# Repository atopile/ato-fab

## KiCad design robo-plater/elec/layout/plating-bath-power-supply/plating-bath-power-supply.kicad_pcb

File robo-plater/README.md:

# robo-plater

A robot to manage plating PCBs

# Circuit Design

## Motor Driver

The feedback for the motor driver is fun. We use the fact that DC brushed motors means there's a convenient current ripple from the mechanical commutation. If we count the pulses in the current ripple, we can determine the position of the motor.

You can make a very simple circuit to do this using a single op-amp, and some discretes, but I've used a second op-amp here because even the cheapest packages seem to come with at least two op-amps.

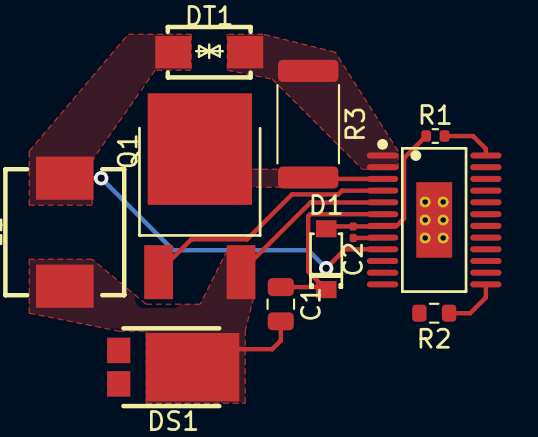
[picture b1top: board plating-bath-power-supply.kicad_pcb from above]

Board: 2 copper layers, 11 parts (0 on the bottom side), 10 nets.

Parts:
C1: 50V 150nF X7R ±10% 0805 Multilayer Ceramic Capaci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; C0805
C2: 6.3V 3uF X5R ±20% 0201 Multilayer Ceramic Capacit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; C0201
D1: ?; SOD-123_L2.8-W1.8-LS3.7-RD
DS1: ?; TO-277B-3_L5.4-W4.1-P1.85-LS6.5-TR
DT1: ?; SMA_L4.4-W2.6-LS5.0-BI
L1: ?; IND-SMD_L7.0-W6.6
Q1: ?; TO-252-2_L6.6-W6.1-P4.57-LS9.9-BR-CW
R1: 62.5mW Thick Film Resistors 50V ±800ppm/℃ ±1% 0Ω 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; R0402
R2: 100mW Thick Film Resistors 75V ±100ppm/℃ ±1% 10kΩ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; R0603
R3: ?; R2512
U1: ?; HTSSOP-24_L7.8-W4.4-P0.65-BL-EP

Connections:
boot1: C1.1, D1.1, U1.6
csn1: Q1.2, R3.2, U1.3
en_uv: R1.1, U1.24
gate1: Q1.1, U1.4
gnd: C2.2, DS1.1, DS1.3, U1.8, U1.17
miso: R2.1, U1.13
sw1: C1.2, DS1.2, L1.1, Q1.3, U1.5
vcc1: C2.1, D1.2, R1.2, U1.7
vcc-1: DT1.1, R3.1, U1.1, U1.2
vcc-2: DT1.2, L1.2, U1.9

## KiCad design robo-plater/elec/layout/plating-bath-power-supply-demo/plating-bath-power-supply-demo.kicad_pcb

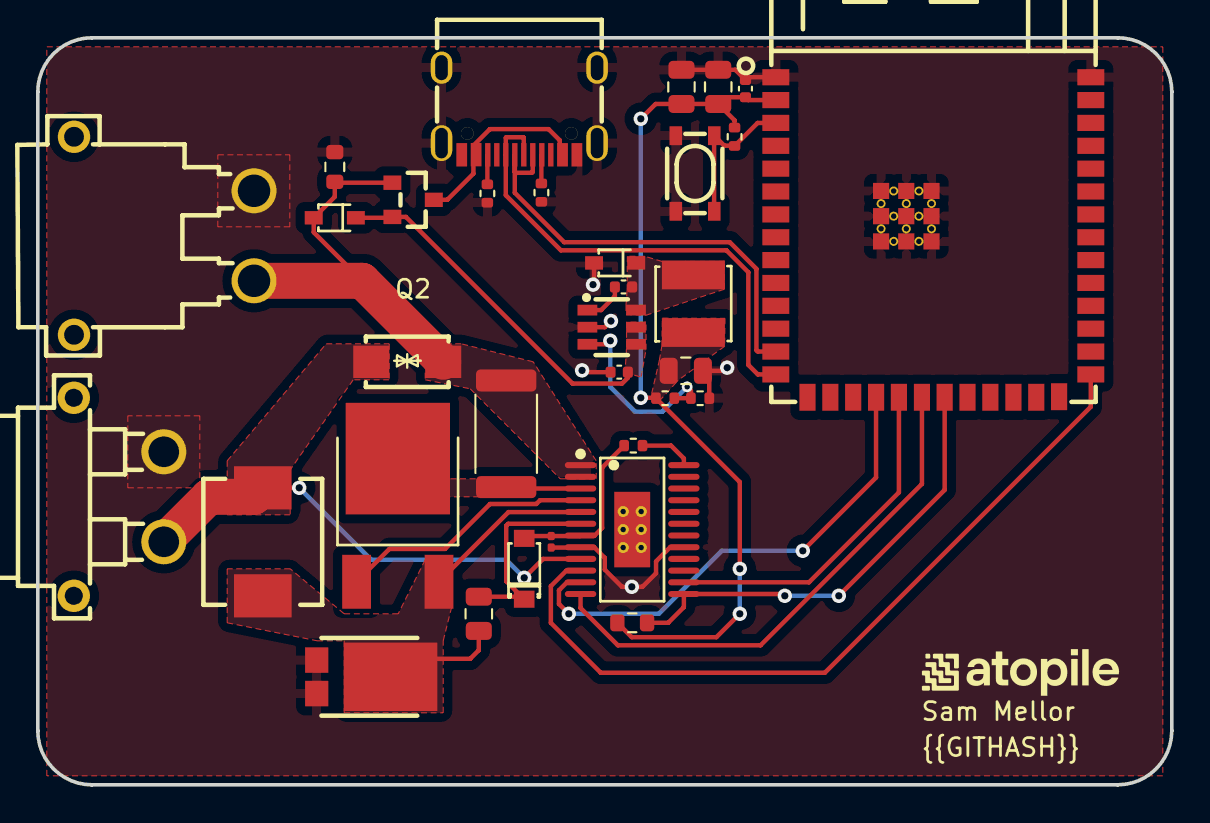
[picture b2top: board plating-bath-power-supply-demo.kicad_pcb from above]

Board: 2 copper layers, 63.0 x 41.5 mm, 33 parts (0 on the bottom side), 25 nets.

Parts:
C1: 6.3V 10uF X5R ±20% 0402 Multilayer Ceramic Capaci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; C0402
C2, C5, C6: 25V 10uF X5R ±10% 0805 Multilayer Ceramic Capacit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; C0805
C3, C4: 16V 100nF X7R ±10% 0402 Multilayer Ceramic Capaci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; C0402
C7: 50V 150nF X7R ±10% 0805 Multilayer Ceramic Capaci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; C0805
C8: 6.3V 3uF X5R ±20% 0201 Multilayer Ceramic Capacit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; C0201
D1: ?; SOD-123_L2.8-W1.8-LS3.7-RD
DS1, DS3: ?; SOD-323_L1.8-W1.3-LS2.5-RD
DS2: ?; TO-277B-3_L5.4-W4.1-P1.85-LS6.5-TR
DT1: ?; SMA_L4.4-W2.6-LS5.0-BI
J1: ?; CONN-TH_XT30PW-M
L1: ?; IND-SMD_L4.0-W4.0
L2: ?; IND-SMD_L7.0-W6.6
Q1: ?; TO-252-2_L6.6-W6.1-P4.57-LS9.9-BR-CW
Q2: ?; SOT-23_L2.9-W1.3-P1.90-LS2.4-BR
R1, R2: 62.5mW Thick Film Resistors 50V ±100ppm/℃ ±1% 4.7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; R0402
R3: 62.5mW Thick Film Resistors 50V ±100ppm/℃ ±1% 14.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; R0402
R4: 62.5mW Thick Film Resistors 50V ±100ppm/℃ ±1% 4.3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; R0402
R5: 62.5mW Thick Film Resistors 50V ±100ppm/℃ ±1% 10k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; R0402
R6: 62.5mW Thick Film Resistors 50V ±800ppm/℃ ±1% 0Ω 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; R0402
R7, R9: 100mW Thick Film Resistors 75V ±100ppm/℃ ±1% 10kΩ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; R0603
R8: ?; R2512
U1: ?; USB-C-SMD_KH-TYPE-C-16P
U2: 0.6A, 42V, 1.1MHz Buck Regulator; SOT-23-6_L2.9-W1.6-P0.95-LS2.8-BR
U3: ?; WIRELM-SMD_ESP32-S3-WROOM-1
U4: ?; KEY-SMD_4P-L4.2-W3.2-P2.20-LS4.6
U5: ?; HTSSOP-24_L7.8-W4.4-P0.65-BL-EP
U6: ?; CONN-TH_XT30PW-F-1

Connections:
boot1: C7.1, D1.1, U5.6
cb: C3.1, U2.1
cc1: R1.1, U1.A5
cc2: R2.1, U1.B5
cs: U3.18, U5.11
csn1: Q1.2, R8.2, U5.3
dm: U1.A7, U1.B7, U3.13
dp: U1.A6, U1.B6, U3.14
en: R5.2, U3.3, U4.1, U4.2
en_uv: R6.1, U5.24
gate1: Q1.1, U5.4
io0: U3.27, U5.10
miso: R7.1, U3.21, U5.13
mosi: U3.19, U5.14
out: R3.2, R4.1, U2.3
plating_supply-vcc: DT1.2, L2.2, U5.9, U6.2
regulator-vcc: C1.1, DS3.1, Q2.2, U2.4, U2.5
regulator-vcc-1: C2.1, C4.1, C5.1, C6.1, L1.2, R3.1, R5.1, R7.2, U3.2
sck: U3.20, U5.12
sw: C3.2, DS1.1, L1.1, U2.6
sw1: C7.2, DS2.2, L2.1, Q1.3, U5.5
usb_conn-vcc: Q2.3, U1.A4, U1.A9, U1.B4, U1.B9
vcc1: C8.1, D1.2, R6.2, U5.7
xt30_input-gnd: C1.2, C2.2, C4.2, C5.2, C6.2, C8.2, DS1.2, DS2.1, DS2.3, J1.1, R1.2, R2.2, R4.2, R9.2, U1.1, U1.2, U1.3, U1.4, U1.A1, U1.A12, U1.B1, U1.B12, U2.2, U3.1, U3.40, U3.41, U4.3, U4.4, U5.8, U5.17, U6.1
xt30_input-vcc: DS3.2, DT1.1, J1.2, Q2.1, R8.1, R9.1, U5.1, U5.2

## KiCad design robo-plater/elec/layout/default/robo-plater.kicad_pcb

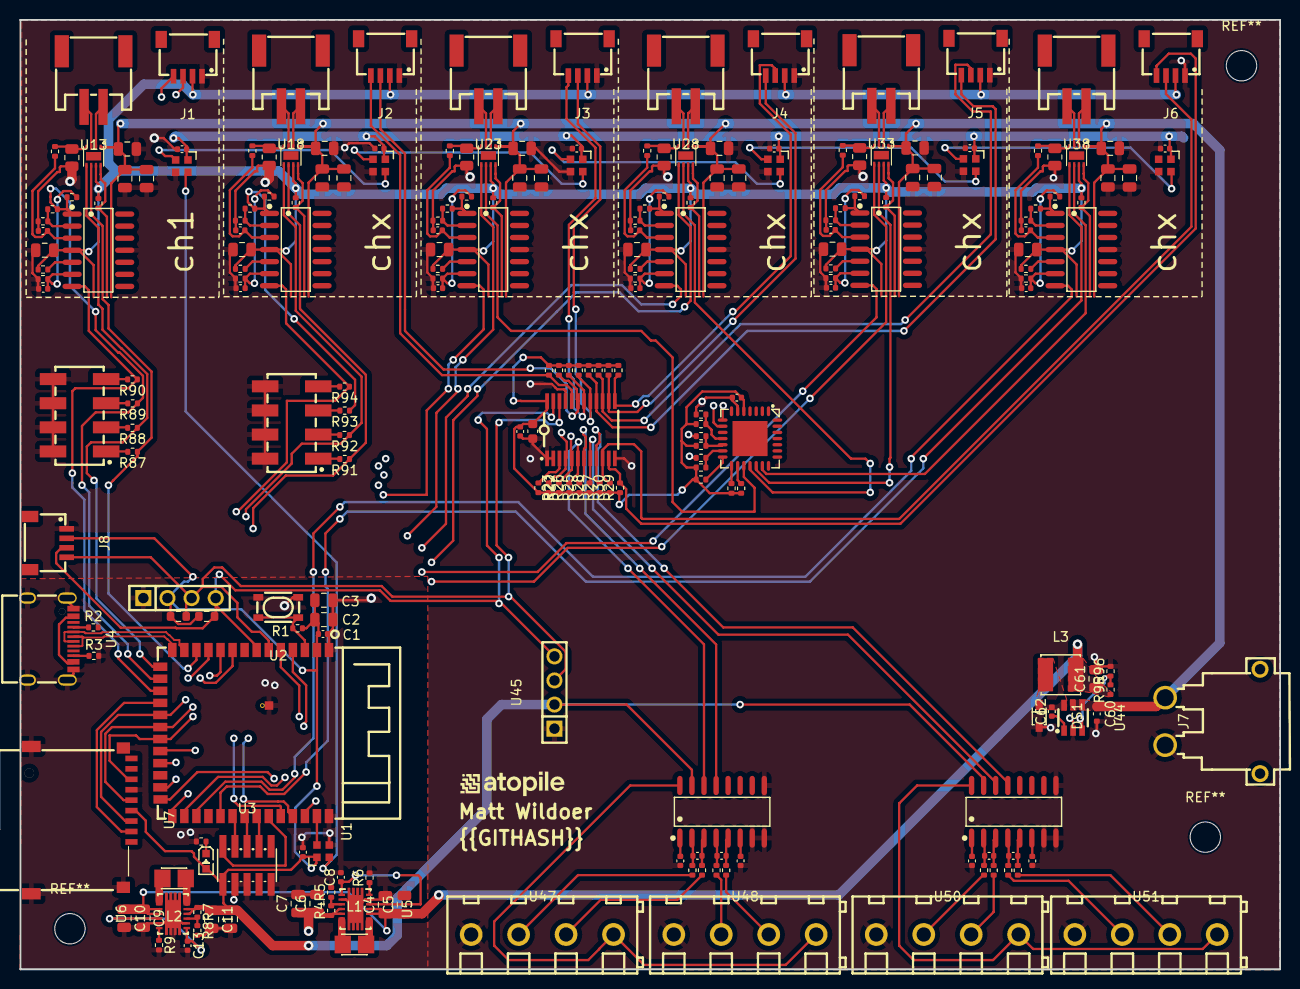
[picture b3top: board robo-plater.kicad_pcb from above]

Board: 4 copper layers, 132.7 x 100.0 mm, 238 parts (0 on the bottom side), 174 nets.

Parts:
C1, C8, C13, C14, C15, C16, C22, C24, C29, C31, C36, C38, C43, C45, C50, C52, C57, C59, C62, C63, C64, C65, C66, C67, C68, C69, C70: 16V 100nF X7R ±10% 0402 Multilayer Ceramic Capaci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; C0402
C2, C3, C4, C5, C6, C7, C9, C10, C11, C12, C18, C19, C20, C21, C25, C26, C27, C28, C32, C33, C34, C35, C39, C40, C41, C42, C46, C47, C48, C49, C53, C54, C55, C56, C61: 25V 10uF X5R ±10% 0805 Multilayer Ceramic Capacit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; C0805
C17: 16V 2.2uF X5R ±10% 0603 Multilayer Ceramic Capaci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; C0603
C23, C30, C37, C44, C51, C58: 25V 1uF X5R ±10% 0402 Multilayer Ceramic Capacito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; C0402
C60: 6.3V 10uF X5R ±20% 0402 Multilayer Ceramic Capaci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; C0402
DS1: ?; SOD-323_L1.8-W1.3-LS2.5-RD
J1, J2, J3, J4, J5, J6, J8: ?; CONN-SMD_4P-P1.00_SM04B-SRSS-TB-LF-SN
J7: ?; CONN-TH_XT30PW-M
L1, L2: ?; IND-SMD_L2.5-W2.0_WPN252012H
L3: ?; IND-SMD_L4.0-W4.0
LED1: ?; LED0603-RD
R1, R13, R14, R15, R16, R17, R18, R19, R20, R21, R22, R23, R24, R25, R26, R27, R28, R29, R30, R31, R32, R33, R34, R35, R36, R37, R38, R39, R47, R55, R63, R71, R79: 62.5mW Thick Film Resistors 50V ±100ppm/℃ ±1% 10k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; R0402
R2, R3: 62.5mW Thick Film Resistors 50V ±100ppm/℃ ±1% 4.7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; R0402
R4: 62.5mW 50V ±100ppm/℃ ±1% 25.5kΩ 0402 Chip Resisto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; R0402
R5: 62.5mW Thick Film Resistors 50V ±100ppm/℃ ±1% 2.8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; R0402
R6, R9, R45, R46, R53, R54, R61, R62, R69, R70, R77, R78, R85, R86: 62.5mW Thick Film Resistors 50V ±100ppm/℃ ±1% 1MΩ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; R0402
R7, R95: 62.5mW Thick Film Resistors 50V ±100ppm/℃ ±1% 23.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; R0402
R8, R96: 62.5mW Thick Film Resistors 50V ±100ppm/℃ ±1% 4.3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; R0402
R10: 62.5mW Thick Film Resistors 50V ±100ppm/℃ ±1% 330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; R0402
R11, R12: 100mW Thick Film Resistors 75V ±100ppm/℃ ±1% 2.7k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; R0603
R40, R48, R56, R64, R72, R80: 125mW Thick Film Resistors 150V ±1% ±400ppm/℃ 1Ω 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; R0805
R41, R49, R57, R65, R73, R81: 62.5mW Thick Film Resistors 50V ±100ppm/℃ ±1% 1.3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; R0402
R42, R50, R58, R66, R74, R82: 62.5mW Thick Film Resistors 50V ±100ppm/℃ ±1% 365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; R0402
R43, R51, R59, R67, R75, R83: 62.5mW Thick Film Resistors 50V ±100ppm/℃ ±1% 36.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; R0402
R44, R52, R60, R68, R76, R84: 62.5mW Thick Film Resistors 50V ±100ppm/℃ ±1% 1.0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; R0402
R87, R88, R89, R90, R91, R92, R93, R94: 62.5mW Thick Film Resistors 50V ±100ppm/℃ ±1% 1kΩ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; R0402
R97, R98, R99, R100, R101, R102, R103, R104: 62.5mW Thick Film Resistors 50V ±100ppm/℃ ±1% 49.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; R0402
U1: ?; WIRELM-SMD_ESP32-S3-WROOM-1
U2: ?; KEY-SMD_4P-L4.2-W3.2-P2.20-LS4.6
U3: ?; HDR-SMD_10P-P1.27-V-M-R2-C5-LS5.3
U4: ?; USB-C-SMD_KH-TYPE-C-16P
U5, U6: ?; VSON-14_L4.0-W3.0-P0.50-BL-EP_TI_DSJ
U7: ?; TF-SMD_TF-01A
U8, U16, U21, U26, U31, U36, U41: ?; LED-SMD_4P-L2.0-W2.0-BR
U9, U45: ?; HDR-TH_4P-P2.54-V-F
U10: ?; QFN-28_L6.0-W6.0-P0.65-BL-EP3.7
U11: ?; TSSOP-24_L7.8-W4.4-P0.65-LS6.4-BL
U12, U17, U22, U27, U32, U37: ?; WSON-8_L2.0-W2.0-P0.50-TL-EP
U13, U18, U23, U28, U33, U38: ?; CONN-SMD_P2.00_S2B-PH-SM4-TB-LF-SN
U14, U19, U24, U29, U34, U39: ?; NetTie-2_SMD_Pad0.25mm
U15, U20, U25, U30, U35, U40: ?; SOIC-14_L8.7-W3.9-P1.27-LS6.0-BL
U42, U43: ?; HDR-SMD_8P-P2.54-V-M-R2-C4-LS7.4
U44: 0.6A, 42V, 1.1MHz Buck Regulator; SOT-23-6_L2.9-W1.6-P0.95-LS2.8-BR
U46, U49: ?; SOP-16_L9.9-W3.9-P1.27-LS6.0-BL
U47, U48, U50, U51: ?; CONN-TH_4P-P5.00_DB127V-5.0-4P-GN-S

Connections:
cathode: LED1.1, R10.1
cb: C62.1, U44.1
cc1: R2.1, U4.A5
cc2: R3.1, U4.B5
ch1.current: R42.1, R44.1, R89.1, U1.16, U15.1
ch1.dir: R87.1, U1.12, U12.6
ch1.led.ic-led_dout: U16.2, U21.4
ch1.motor_driver-enable: R39.1, U12.8
ch1.motor_driver._shunt_nettie-_shunt_gnd: C22.2, R43.2, U14.1
ch1.motor_driver.driver-_shunt_high: R40.1, R41.1, U12.4
ch1.motor_driver.driver-out1: U12.2, U13.1
ch1.motor_driver.driver-out2: U12.3, U13.2
ch1.motor_driver.op_amp-in1_minus: R42.2, R43.1, U15.2
ch1.motor_driver.op_amp-in1_plus: C22.1, R41.2, U15.3
ch1.motor_driver.op_amp-in2_minus: C23.1, R44.2, R46.1, U15.6
ch1.motor_driver.op_amp-in2_plus: R45.1, U15.5
ch1.pulses: R90.1, U1.17, U15.7
ch1.pwm: R88.1, U1.15, U12.5
ch1_debug.header-_1: R87.2, U42.1
ch1_debug.header-_3: R88.2, U42.3
ch1_debug.header-_5: R89.2, U42.5
ch1_debug.header-_7: R90.2, U42.7
ch2.current: R50.1, R52.1, R93.1, U20.1
ch2.dir: R91.1, U1.10, U17.6
ch2.led.ic-led_dout: U21.2, U26.4
ch2.motor_driver-enable: R47.1, U17.8
ch2.motor_driver._shunt_nettie-_shunt_gnd: C29.2, R51.2, U19.1
ch2.motor_driver.driver-_shunt_high: R48.1, R49.1, U17.4
ch2.motor_driver.driver-out1: U17.2, U18.1
ch2.motor_driver.driver-out2: U17.3, U18.2
ch2.motor_driver.op_amp-in1_minus: R50.2, R51.1, U20.2
ch2.motor_driver.op_amp-in1_plus: C29.1, R49.2, U20.3
ch2.motor_driver.op_amp-in2_minus: C30.1, R52.2, R54.1, U20.6
ch2.motor_driver.op_amp-in2_plus: R53.1, U20.5
ch2.pulses: R94.1, U1.11, U20.7
ch2.pwm: R92.1, U1.9, U17.5
ch2_debug.header-_1: R91.2, U43.1
ch2_debug.header-_3: R92.2, U43.3
ch2_debug.header-_5: R93.2, U43.5
ch2_debug.header-_7: R94.2, U43.7
ch3.dir: U10.17, U22.6
ch3.led.ic-led_dout: U26.2, U31.4
ch3.motor_driver-current: R58.1, R60.1, U25.1
ch3.motor_driver-enable: R55.1, U22.8
ch3.motor_driver._shunt_nettie-_shunt_gnd: C36.2, R59.2, U24.1
ch3.motor_driver.driver-_shunt_high: R56.1, R57.1, U22.4
ch3.motor_driver.driver-out1: U22.2, U23.1
ch3.motor_driver.driver-out2: U22.3, U23.2
ch3.motor_driver.op_amp-in1_minus: R58.2, R59.1, U25.2
ch3.motor_driver.op_amp-in1_plus: C36.1, R57.2, U25.3
ch3.motor_driver.op_amp-in2_minus: C37.1, R60.2, R62.1, U25.6
ch3.motor_driver.op_amp-in2_plus: R61.1, U25.5
ch3.pulses: U1.37, U25.7
ch3.pwm: U1.22, U22.5
ch4.dir: U10.18, U27.6
ch4.led.ic-led_dout: U31.2, U36.4
ch4.motor_driver-current: R66.1, R68.1, U30.1
ch4.motor_driver-enable: R63.1, U27.8
ch4.motor_driver._shunt_nettie-_shunt_gnd: C43.2, R67.2, U29.1
ch4.motor_driver.driver-_shunt_high: R64.1, R65.1, U27.4
ch4.motor_driver.driver-out1: U27.2, U28.1
ch4.motor_driver.driver-out2: U27.3, U28.2
ch4.motor_driver.op_amp-in1_minus: R66.2, R67.1, U30.2
ch4.motor_driver.op_amp-in1_plus: C43.1, R65.2, U30.3
ch4.motor_driver.op_amp-in2_minus: C44.1, R68.2, R70.1, U30.6
ch4.motor_driver.op_amp-in2_plus: R69.1, U30.5
ch4.pulses: U1.23, U30.7
ch4.pwm: U1.25, U27.5
ch5.dir: U10.19, U32.6
ch5.led.ic-led_dout: U36.2, U41.4
ch5.motor_driver-current: R74.1, R76.1, U35.1
ch5.motor_driver-enable: R71.1, U32.8
ch5.motor_driver._shunt_nettie-_shunt_gnd: C50.2, R75.2, U34.1
ch5.motor_driver.driver-_shunt_high: R72.1, R73.1, U32.4
ch5.motor_driver.driver-out1: U32.2, U33.1
ch5.motor_driver.driver-out2: U32.3, U33.2
ch5.motor_driver.op_amp-in1_minus: R74.2, R75.1, U35.2
ch5.motor_driver.op_amp-in1_plus: C50.1, R73.2, U35.3
ch5.motor_driver.op_amp-in2_minus: C51.1, R76.2, R78.1, U35.6
ch5.motor_driver.op_amp-in2_plus: R77.1, U35.5
ch5.pulses: U1.26, U35.7
ch5.pwm: U1.28, U32.5
ch6.dir: U10.20, U37.6
ch6.motor_driver-current: R82.1, R84.1, U40.1
ch6.motor_driver-enable: R79.1, U37.8
ch6.motor_driver._shunt_nettie-_shunt_gnd: C57.2, R83.2, U39.1
ch6.motor_driver.driver-_shunt_high: R80.1, R81.1, U37.4
ch6.motor_driver.driver-out1: U37.2, U38.1
ch6.motor_driver.driver-out2: U37.3, U38.2
ch6.motor_driver.op_amp-in1_minus: R82.2, R83.1, U40.2
ch6.motor_driver.op_amp-in1_plus: C57.1, R81.2, U40.3
ch6.motor_driver.op_amp-in2_minus: C58.1, R84.2, R86.1, U40.6
ch6.motor_driver.op_amp-in2_plus: R85.1, U40.5
ch6.pulses: U1.29, U40.7
ch6.pwm: U1.31, U37.5
cs: U1.18, U7.2
en: R1.2, U1.3, U2.1, U2.2
gnd: C1.2, C2.2, C3.2, C4.2, C5.2, C6.2, C7.2, C8.2, C9.2, C10.2, C11.2, C12.2, C13.2, C14.2, C15.2, C16.2, C17.2, C18.2, C19.2, C20.2, C21.2, C23.2, C24.2, C25.2, C26.2, C27.2, C28.2, C30.2, C31.2, C32.2, C33.2, C34.2, C35.2, C37.2, C38.2, C39.2, C40.2, C41.2, C42.2, C44.2, C45.2, C46.2, C47.2, C48.2, C49.2, C51.2, C52.2, C53.2, C54.2, C55.2, C56.2, C58.2, C59.2, C60.2, C61.2, C63.2, C64.2, C67.2, C68.2, DS1.2, J1.1, J2.1, J3.1, J4.1, J5.1, J6.1, J7.1, J8.1, R2.2, R3.2, R5.2, R6.2, R8.2, R9.2, R10.2, R14.2, R16.2, R18.2, R40.2, R46.2, R48.2, R54.2, R56.2, R62.2, R64.2, R70.2, R72.2, R78.2, R80.2, R86.2, R96.2, U1.1, U1.40, U1.41, U2.3, U2.4, U3.3, U3.5, U3.9, U4.1, U4.2, U4.3, U4.4, U4.A1, U4.A12, U4.B1, U4.B12, U5.2, U5.13, U5.15, U6.2, U6.13, U6.15, U7.6, U7.10, U7.11, U7.12, U7.13, U8.3, U9.1, U10.6, U11.1, U11.2, U11.12, U11.21, U14.2, U15.11, U16.3, U19.2, U20.11, U21.3, U24.2, U25.11, U26.3, U29.2, U30.11, U31.3, U34.2, U35.11, U36.3, U39.2, U40.11, U41.3, U42.2, U42.4, U42.6, U42.8, U43.2, U43.4, U43.6, U43.8, U44.2, U45.1, U46.7, U46.8, U46.9, U47.1, U48.1, U49.7, U49.8, U49.9, U50.1, U51.1
i2c_mux.ic-scl: J1.4, R23.2, U11.5
i2c_mux.ic-scl-1: R25.2, U11.7, U46.13
i2c_mux.ic-scl-2: R27.2, U11.9, U49.13
i2c_mux.ic-scl-3: J6.4, R29.2, U11.11
i2c_mux.ic-scl-4: J4.4, R31.2, U11.14
i2c_mux.ic-scl-5: J5.4, R33.2, U11.16
i2c_mux.ic-scl-6: J3.4, R35.2, U11.18
i2c_mux.ic-scl-7: J2.4, R37.2, U11.20
i2c_mux.ic-sda: J1.3, R24.2, U11.4
i2c_mux.ic-sda-1: R26.2, U11.6, U46.14
i2c_mux.ic-sda-2: R28.2, U11.8, U49.14
i2c_mux.ic-sda-3: J6.3, R30.2, U11.10
i2c_mux.ic-sda-4: J4.3, R32.2, U11.13
i2c_mux.ic-sda-5: J5.3, R34.2, U11.15
i2c_mux.ic-sda-6: J3.3, R36.2, U11.17
i2c_mux.ic-sda-7: J2.3, R38.2, U11.19
int_a: R20.2, U10.16
int_b: R21.2, U10.15
io1: U1.39, U8.4
io_expander.a0_pull-center: R13.2, R14.1, U10.11
io_expander.a1_pull-center: R15.2, R16.1, U10.12
io_expander.a2_pull-center: R17.2, R18.1, U10.13
io_expander.ic-reset: R19.2, U10.14
load_cell_amp_1-n: R97.1, U47.2
load_cell_amp_1-n-1: R99.1, U48.2
load_cell_amp_1-p: R98.1, U47.3
load_cell_amp_1-p-1: R100.1, U48.3
load_cell_amp_1-vcc: U46.16, U47.4, U48.4
load_cell_amp_1.ic-refp: C64.1, U46.1
load_cell_amp_1.ic-vbg: C63.1, U46.6
load_cell_amp_1.ic-vin1n: C65.1, R97.2, U46.2
load_cell_amp_1.ic-vin1p: C65.2, R98.2, U46.3
load_cell_amp_1.ic-vin2n: C66.1, R99.2, U46.4
load_cell_amp_1.ic-vin2p: C66.2, R100.2, U46.5
load_cell_amp_2-n: R101.1, U50.2
load_cell_amp_2-n-1: R103.1, U51.2
load_cell_amp_2-p: R102.1, U50.3
load_cell_amp_2-p-1: R104.1, U51.3
load_cell_amp_2-vcc: U49.16, U50.4, U51.4
load_cell_amp_2.ic-refp: C68.1, U49.1
load_cell_amp_2.ic-vbg: C67.1, U49.6
load_cell_amp_2.ic-vin1n: C69.1, R101.2, U49.2
load_cell_amp_2.ic-vin1p: C69.2, R102.2, U49.3
load_cell_amp_2.ic-vin2n: C70.1, R103.2, U49.4
load_cell_amp_2.ic-vin2p: C70.2, R104.2, U49.5
miso: U1.21, U7.7
mosi: U1.19, U7.3
nc: U10.7, U10.10
reset_: R22.1, U11.3
sck: U1.20, U7.5
supply_5v.feedback_div-out: R95.2, R96.1, U44.3
sw: C62.2, DS1.1, L3.1, U44.6
tck: U1.32, U3.4
tdi: U1.34, U3.8
tdo: U1.33, U3.6
tms: U1.35, U3.2
uc-vcc: C4.1, C5.1, C9.1, C10.1, C61.1, L3.2, R95.1, U5.10, U5.11, U6.10, U6.11
uc._3v3_reg.feedback_div-out: R7.2, R8.1, U6.3
uc._3v3_reg.ic-l1: L2.1, U6.8, U6.9
uc._3v3_reg.ic-l2: L2.2, U6.6, U6.7
uc._3v3_reg.ic-pg: R9.1, U6.14
uc._3v3_reg.ic-vina: C13.1, U6.1, U6.12
uc._5v_reg.feedback_div-out: R4.2, R5.1, U5.3
uc._5v_reg.ic-l1: L1.1, U5.8, U5.9
uc._5v_reg.ic-l2: L1.2, U5.6, U5.7
uc._5v_reg.ic-pg: R6.1, U5.14
uc._5v_reg.ic-vina: C8.1, U5.1, U5.12
uc._led.ic-led_dout: U8.2, U16.4
uc.uc.ic-scl: J8.4, R12.1, U1.6, U9.3, U10.8, U11.22, U45.3
uc.uc.ic-sda: J8.3, R11.1, U1.7, U9.4, U10.9, U11.23, U45.4
uc.usb_conn-vcc: U4.A4, U4.A9, U4.B4, U4.B9
usb+: U1.14, U4.A6, U4.B6
usb-: U1.13, U4.A7, U4.B7
vcc: C18.1, C19.1, C20.1, C25.1, C26.1, C27.1, C32.1, C33.1, C34.1, C39.1, C40.1, C41.1, C46.1, C47.1, C48.1, C53.1, C54.1, C55.1, C60.1, J7.2, U12.1, U17.1, U22.1, U27.1, U32.1, U37.1, U44.4, U44.5
vcc-1: C6.1, C7.1, C24.1, C31.1, C38.1, C45.1, C52.1, C59.1, R4.1, U5.4, U5.5, U16.1, U21.1, U26.1, U31.1, U36.1, U41.1
vcc-2: C1.1, C2.1, C3.1, C11.1, C12.1, C14.1, C15.1, C16.1, C17.1, C21.1, C28.1, C35.1, C42.1, C49.1, C56.1, J1.2, J2.2, J3.2, J4.2, J5.2, J6.2, J8.2, LED1.2, R1.1, R7.1, R11.2, R12.2, R13.1, R15.1, R17.1, R19.1, R20.1, R21.1, R22.2, R23.1, R24.1, R25.1, R26.1, R27.1, R28.1, R29.1, R30.1, R31.1, R32.1, R33.1, R34.1, R35.1, R36.1, R37.1, R38.1, R39.2, R45.2, R47.2, R53.2, R55.2, R61.2, R63.2, R69.2, R71.2, R77.2, R79.2, R85.2, U1.2, U3.1, U6.4, U6.5, U7.4, U8.1, U9.2, U10.5, U11.24, U12.7, U15.4, U17.7, U20.4, U22.7, U25.4, U27.7, U30.4, U32.7, U35.4, U37.7, U40.4, U45.2, U46.15, U49.15

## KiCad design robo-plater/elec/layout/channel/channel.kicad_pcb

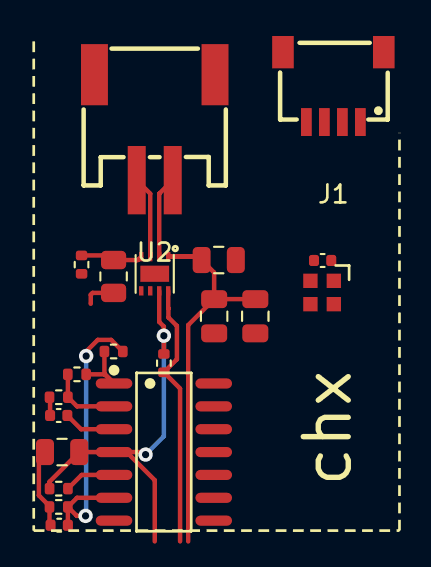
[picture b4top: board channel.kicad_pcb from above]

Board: 2 copper layers, 21 parts (0 on the bottom side), 15 nets.

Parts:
C1, C2, C3, C4: 25V 10uF X5R ±10% 0805 Multilayer Ceramic Capacit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; C0805
C5, C7: 16V 100nF X7R ±10% 0402 Multilayer Ceramic Capaci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; C0402
C6: 25V 1uF X5R ±10% 0402 Multilayer Ceramic Capacito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; C0402
J1: ?; CONN-SMD_4P-P1.00_SM04B-SRSS-TB-LF-SN
R1: 62.5mW Thick Film Resistors 50V ±100ppm/℃ ±1% 10k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; R0402
R2: 125mW Thick Film Resistors 150V ±1% ±400ppm/℃ 1Ω 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; R0805
R3: 62.5mW Thick Film Resistors 50V ±100ppm/℃ ±1% 1.3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; R0402
R4: 62.5mW Thick Film Resistors 50V ±100ppm/℃ ±1% 365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; R0402
R5: 62.5mW Thick Film Resistors 50V ±100ppm/℃ ±1% 36.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; R0402
R6: 62.5mW Thick Film Resistors 50V ±100ppm/℃ ±1% 1.0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; R0402
R7, R8: 62.5mW Thick Film Resistors 50V ±100ppm/℃ ±1% 1MΩ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; R0402
U1: ?; WSON-8_L2.0-W2.0-P0.50-TL-EP
U2: ?; CONN-SMD_P2.00_S2B-PH-SM4-TB-LF-SN
U3: ?; NetTie-2_SMD_Pad0.25mm
U4: ?; SOIC-14_L8.7-W3.9-P1.27-LS6.0-BL
U5: ?; LED-SMD_4P-L2.0-W2.0-BR

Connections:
_shunt_gnd: C5.2, R5.2, U3.1
_shunt_high: R2.1, R3.1, U1.4
current: R4.1, R6.1, U4.1
enable: R1.1, U1.8
in1_minus: R4.2, R5.1, U4.2
in1_plus: C5.1, R3.2, U4.3
in2_minus: C6.1, R6.2, R8.1, U4.6
in2_plus: R7.1, U4.5
led.ic-gnd: C7.2, U5.3
led.ic-vcc: C7.1, U5.1
motor_driver-gnd: C1.2, C2.2, C3.2, C4.2, C6.2, J1.1, R2.2, R8.2, U3.2, U4.11
motor_driver-vcc: C1.1, C2.1, C3.1, U1.1
motor_driver-vcc-1: C4.1, J1.2, R1.2, R7.2, U1.7, U4.4
out1: U1.2, U2.1
out2: U1.3, U2.2

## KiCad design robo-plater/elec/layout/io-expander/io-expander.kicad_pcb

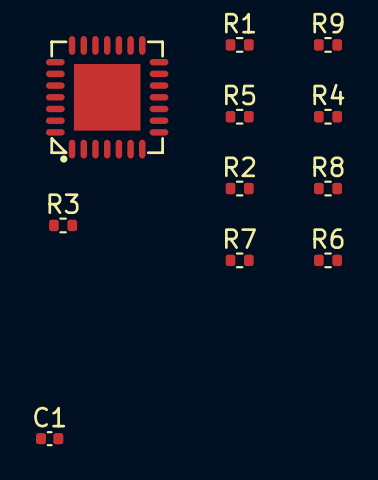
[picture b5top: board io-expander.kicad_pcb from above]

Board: 2 copper layers, 11 parts (0 on the bottom side), 9 nets, no tracks yet.

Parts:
C1: 16V 100nF X7R ±10% 0402 Multilayer Ceramic Capaci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; C0402
R1, R2, R3, R4, R5, R6, R7, R8, R9: 62.5mW Thick Film Resistors 50V ±100ppm/℃ ±1% 10k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; R0402
U1: ?; QFN-28_L6.0-W6.0-P0.65-BL-EP3.7

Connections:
a0_pull-center: R1.2, R2.1, U1.11
a1_pull-center: R3.2, R4.1, U1.12
a2_pull-center: R5.2, R6.1, U1.13
gnd: C1.2, R2.2, R4.2, R6.2, U1.6
int_a: R8.2, U1.16
int_b: R9.2, U1.15
nc: U1.7, U1.10
reset: R7.2, U1.14
vcc: C1.1, R1.1, R3.1, R5.1, R7.1, R8.1, R9.1, U1.5

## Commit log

2024-09-13 Add .gitignore and remove .venv from repo
2024-10-15 Init + MotorDriver
2024-10-15 Layout MotorDriver and group layout
2024-10-15 Update feedback circuit
2024-10-15 Two motor driver channels with debug headers
2024-10-15 Add 12V input and power connector
2024-10-16 Link generics
2024-10-16 Add io expander
2024-10-16 Reorganise into channels
2024-10-17 Add stemma/quuic connectors and load cell amps
2024-10-18 Layout v0.1 done
2024-10-18 CI workflows for robo-plater
2024-10-18 Remove DS_Store
2024-10-18 Change working dir for job
2024-10-18 Add plating bath power supply module
2024-10-19 Add plating bath power supply demo board
2024-10-20 Remove outputs
2024-10-20 Use standard python gitignore
2024-10-20 Move drill parsing to utils file
2024-10-21 Print logging via log, rather than print
2024-10-21 Drill holes to svg!
2024-10-24 initial calibration tests
2024-10-25 Test calibration examination
2024-10-29 Setup platformio project
2024-10-30 Dot generation working. Finds points. Generally all good! Need better projection correction
2024-10-30 Unwarping needs a little more love
2024-10-30 Undistorting with undistort sucks
2024-10-30 Late late at night
2024-10-30 Manual R matrix didn't work
2024-10-30 Most basic remapping not working
2024-10-30 Hide aider stuff
2024-10-30 Worked with scan
2024-10-31 Got another one working. Fingers crossed
2024-10-31 Add working homography
2024-10-31 Basis for processing for KiCAD outputs to shoot
2024-10-31 Seemingly regressions
2024-11-02 Finding things
2024-11-02 adding working sandbox for remap + cubic interpolation
2024-11-03 Decent compensation mapping
2024-11-03 Add closest zipping, histogram calculations and scatter plotting
2024-11-03 The motherfuckin dots line up!!!!
2024-11-03 Working image remapper
2024-11-03 Save first top calibration
2024-11-03 Add remap_targets CLI script
2024-11-07 Fix CI
2024-11-08 Unlock deps to upgrade a few things. I'll leave them open since it's a fast-n-loose internal pacakge
